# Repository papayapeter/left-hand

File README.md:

# left-hand
a robotic hand that reacts to touch by gripping the touching hand

documentation: [https://zenogries.com/portfolio/wasmachstduda/](https://zenogries.com/portfolio/wasmachstduda/)

## libraries
* [Metro](https://github.com/thomasfredericks/Metro-Arduino-Wiring) by thomasfredericks
* [AccelStepper](http://www.airspayce.com/mikem/arduino/AccelStepper/) by Mike McCauley

## hardware
* [teensy lc ](https://www.pjrc.com/teensy/teensyLC.html)
* [a4988 stepper driver](https://www.pololu.com/product/1182)
* [nema 17 stepper](https://www.ebay.de/itm/Nema-17-Stepper-Motor-Schrittmotor-26Ncm-12V-0-4A-4-wire-1m-cable-3D-Printer/392163408983?hash=item5b4ec2bc57:g:sAsAAOSwfB9b2Q9~)
* carrier pcb and aluminium skeleton designed by me
* silikon glove

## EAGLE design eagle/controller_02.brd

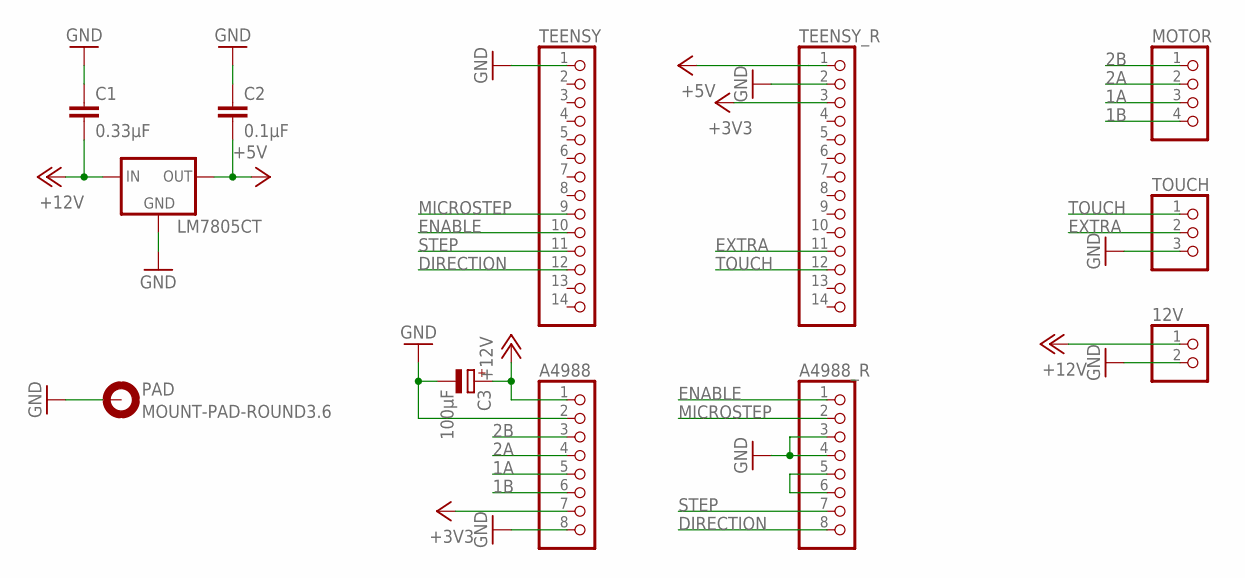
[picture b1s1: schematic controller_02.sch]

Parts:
12V: PINHD-1X2; 1X02
A4988, A4988_R: PINHD-1X8; 1X08
C1: 0.33µF; C025-025X050
C2: 0.1µF; C025-025X050
C3: 100µF; E3,5-8
LM7805CT: 78XXL
MOTOR: PINHD-1X4; 1X04
PAD: MOUNT-PAD-ROUND3.6; 3,6-PAD
TEENSY: PINHD-1X14; 1X14
TEENSY_R: PINHD-1X14; 1X14
TOUCH: PINHD-1X3; 1X03

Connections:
1A: A4988.5, MOTOR.3
1B: A4988.6, MOTOR.4
2A: A4988.4, MOTOR.2
2B: A4988.3, MOTOR.1
+3V3: A4988.7, TEENSY_R.3
+5V: C2.2, LM7805CT.OUT, TEENSY_R.1
+12V: 12V.1, A4988.1, C1.2, C3.+, LM7805CT.IN
DIRECTION: A4988_R.8, TEENSY.12
ENABLE: A4988_R.1, TEENSY.10
EXTRA: TEENSY_R.11, TOUCH.2
GND: 12V.2, A4988.2, A4988.8, A4988_R.3, A4988_R.4, C1.1, C2.1, C3.-, LM7805CT.GND, PAD.B3,6, TEENSY.1, TEENSY_R.2, TOUCH.3
MICROSTEP: A4988_R.2, TEENSY.9
unnamed: A4988_R.5, A4988_R.6
STEP: A4988_R.7, TEENSY.11
TOUCH: TEENSY_R.12, TOUCH.1

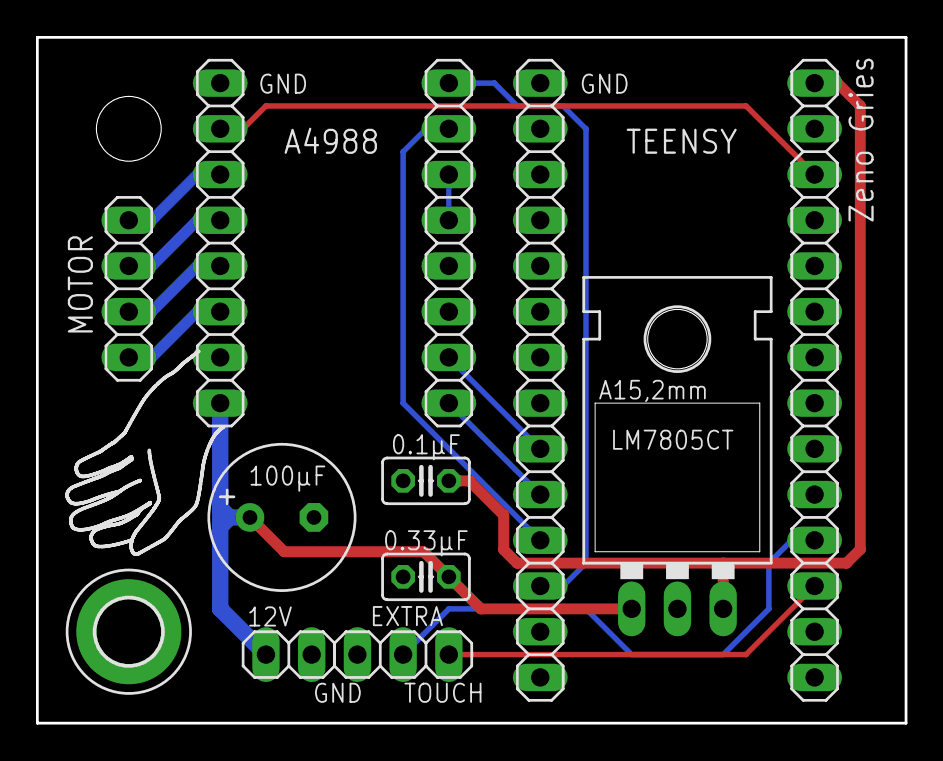
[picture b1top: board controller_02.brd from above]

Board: 2 copper layers, 48.3 x 38.1 mm, 12 parts (0 on the bottom side), 15 nets.

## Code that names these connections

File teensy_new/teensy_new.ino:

// *** Zeno Gries - 2018
// *** Die Hände R2.0

#include "hand.h"

// pins ------------------------------------------------------------------------
const uint8_t MICROSTEP = 7;
const uint8_t ENABLE = 8;
const uint8_t STEP = 9;
const uint8_t DIRECTION = 10;
const uint8_t SEED = 14;
const uint8_t TOUCH = 15;
const uint8_t SWITCH = 16;
const uint8_t LED = 13;

// constants -------------------------------------------------------------------
// motor
const uint16_t motorFailsafe = 300;                 // when to stop moving during calibration
const uint16_t motorLimit = 185;                    // what should be the calibrated position
const uint16_t motorMax = 180;                      // what should be the maximum position (always less than the calibrated position)
const uint16_t motorAcceleration = 50;              // how fast does the motor accelerate during closing?
const uint16_t motorMaxSpeed = 50;                  // how fast will the motor go during closing?
const uint16_t motorAccelerationBack = 25;          // how fast does the motor accelerate during opening?
const uint16_t motorMaxSpeedBack = 25;              // how fast will the motor go during opening?
const uint16_t motorAccelerationCalibration = 2000; // how fast does the motor accelerate during calibration?
const uint16_t motorMaxSpeedCalibration = 20;       // how fast will the motor go during calibration?
const uint16_t motorRemainOverstep = 10;             // how many steps will the motor do after the audience let go?
const uint16_t motorRemainTime = 1000;               // how long does the hand remain still aufter being let go?
const uint16_t motorRemainThreshhold = 80;          // from which position on does the motor "remain"?

const uint16_t motorMaxCome = 50;                   // full closed position if the "come here" gesture
const uint16_t motorComeTime = 8000;                // duration of the "come here" gesture (full period)

const uint16_t motorWiggleTime = 200;               // wiggle interval (when hand is closed)
const uint16_t motorWiggleMagnitude = 4;            // wiggle magnitude (when hand is closed)

// touch
const uint16_t touchThreshhold = 200;               // how sensitive is the hand towards touch?
const uint16_t calibrationLength = 80;              // how many intervals to read for calibration?
const uint16_t pauseLength = 500;                   // how many intervals between touch and calibration?
const uint16_t touchLength = 20;                    // how many intervals to read for touch?

// objects ---------------------------------------------------------------------
Hand hand(MICROSTEP, ENABLE, STEP, DIRECTION, SEED, TOUCH, SWITCH, LED);

// variables -------------------------------------------------------------------
HandState state = OPENING;

uint32_t timeToCalibration;

// setup -----------------------------------------------------------------------
void setup()
{
  hand.setMotor(motorFailsafe,
                motorLimit,
                motorMax,
                motorAcceleration,
                motorMaxSpeed,
                motorAccelerationBack,
                motorMaxSpeedBack,
                motorAccelerationCalibration,
                motorMaxSpeedCalibration,
                motorRemainOverstep,
                motorRemainTime,
                motorRemainThreshhold,
                motorMaxCome,
                motorComeTime,
                motorWiggleTime,
                motorWiggleMagnitude);

  hand.setTouch(touchThreshhold,
                calibrationLength,
                pauseLength,
                touchLength);

  hand.initialize(true, true, 100);

  hand.calibrate();

  hand.fill(5000);

  timeToCalibration = 90000 + random(30000);
}

// loop ------------------------------------------------------------------------
void loop()
{
  if (hand.feel())
  {
    if (state == OPENING)
      hand.close();
  }
  else
  {
    if (state == CLOSING)
      hand.open();
  }

  if (millis() > hand.getLastTouched() + timeToCalibration)
  {
    timeToCalibration = 90000 + random(30000);

    hand.calibrate();
  }

  state = hand.run();
}

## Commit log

2019-06-20 Create LICENSE
2020-10-03 added object oriented script
2020-10-03 added setup
2020-10-03 started script
2020-10-05 added all needed functions
2020-10-05 fleshed out
2020-10-11 finished basic firmware without finetuning
2020-10-21 reversed touchstack filling and calibration at the begining
2020-10-24 changed sensitivity
2020-10-24 exchanged old code for new object oriented code
2020-10-24 removed the random library elements from the class
2020-10-24 renamed folder
2020-10-26 added safety hand release
2020-10-27 lowered threshold
